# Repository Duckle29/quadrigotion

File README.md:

Quadrigotion: Multiple Motor Drivers, two connectors
============================================================

Often it is useful to have all the motor drivers needed for a machine
on a separate circuit board to be able to mount it to a heatsink or close
to the action. This is what this project is about.
The name **Quadrigotion** is a word amalgamated from 'Quadriga' (Four
horses powering a chariot) and 'Motion'.

Motivation for this project to have motor drivers easily replacable and
testable on my various 3D printers and CNC machines. Since I am also
[developing motion control software][BeagleG], I might have an unusual
high demand for this :)

The idea is to have a common connector type, described below, and various
implementations of that concept. The first implementation is using a TMC2660,
which is the 'big brother' of the more well-known TMC2100.

Other implementations are conceivable e.g. with Pololu modules, DRV8825, or
super high current and voltage drivers for heavy CNC machines.
Implementations can be super bare-bone and not use the SPI connection or
could be configured via SPI using a shift-register and digital potentiometers
if the chips can't be configured with SPI directly.
While the first Quadrigotion implementation happens to also have four motor
drivers, this could of course extend in the future.

The Connector
--------------

##TO BE EDITED TO REFLECT USE OF SMOOTHIE GADGETEER PORTS

The digital input is provided with an IDC connector with 16 pins (2x8) or
20 pins (2x10).
It features a SPI bus to send configuration data and also read motor/driver
status (the actual protocol is of implementation-dependent, but they all can
share the same hardware interface).

| Desc               | Pin | Pin | Desc
|-------------------:|:---:|:---:|:-----------------------------
|               GND  |   1 |   2 | VCC (3.3V-5V)
| All Motors ~Enable |   3 |   4 | (not connected; reserved for fault-out)
|          ~CS (SPI) |   5 |   6 | CLK (SPI)
|         MISO (SPI) |   7 |   8 | MOSI (SPI)
|            Step #1 |   9 |  10 | Dir #1
|            Step #2 |  11 |  12 | Dir #2
|            Step #3 |  13 |  14 | Dir #3
|            Step #4 |  15 |  16 | Dir #4 -------- END IDC 16 variant
|            Step #5 |  17 |  18 | Dir #5
|            Step #6 |  19 |  20 | Dir #6 -------- END IDC 20 variant

It is easy to see that extending the driver count would just require a wider
IDC connector; the serial configuration interface can deal with any
number. A 16 pin IDC connector allows for 4 steppers, the next configuration
with 20 pins would allow for six drivers.

A single Enable-pin is provided that affects all drivers. This makes it easy
to wire up that signal directly e.g. for emergency buttons.
If more individual control of each driver is needed, this can be done via
the SPI connection.

The fast signals for each stepper, step and dir, are provided in
a parallel input with two lines per stepper.

A Quadrigotion connector has a single ChipSelect signal; multiple drivers
on each implementation have to share that bus, e.g. by internally being
organized as a shift register that latches when ~CS goes high again.

One pin (pin 4) is not connected yet, but it is reserved for fault detection
output (e.g stalling, overheating or over-current).

In an upcoming project, I'll build a breakout board to work with [BeagleG].

TMC2660 Implementation
----------------------

The first implementation is based on the TMC2660, a feature-rich motor driver
that can drive up to 4A (2.8A RMS). The 40mmx125mm PCB is a four layer board
which duals as heat conductor for cooling. Multiple M2.5 mounting holes allow
to firmly mount it to a heatsink and get even pressure to individual silicone
heatsink pads.
Power is provided via a 4-pin JST VH connector (3.96mm pitch),
circuit protected with an automotive ATC Mini 297 blade fuse.

You find the gerbers in the [fab/](./fab) directory. Board is also
[shared on OshPark]. Cave: since this is the very first version, no
testing has been done yet with a physical board.

[BeagleG]: https://github.com/hzeller/beagleg
[shared on OshPark]: https://oshpark.com/shared_projects/M0SQCRdL

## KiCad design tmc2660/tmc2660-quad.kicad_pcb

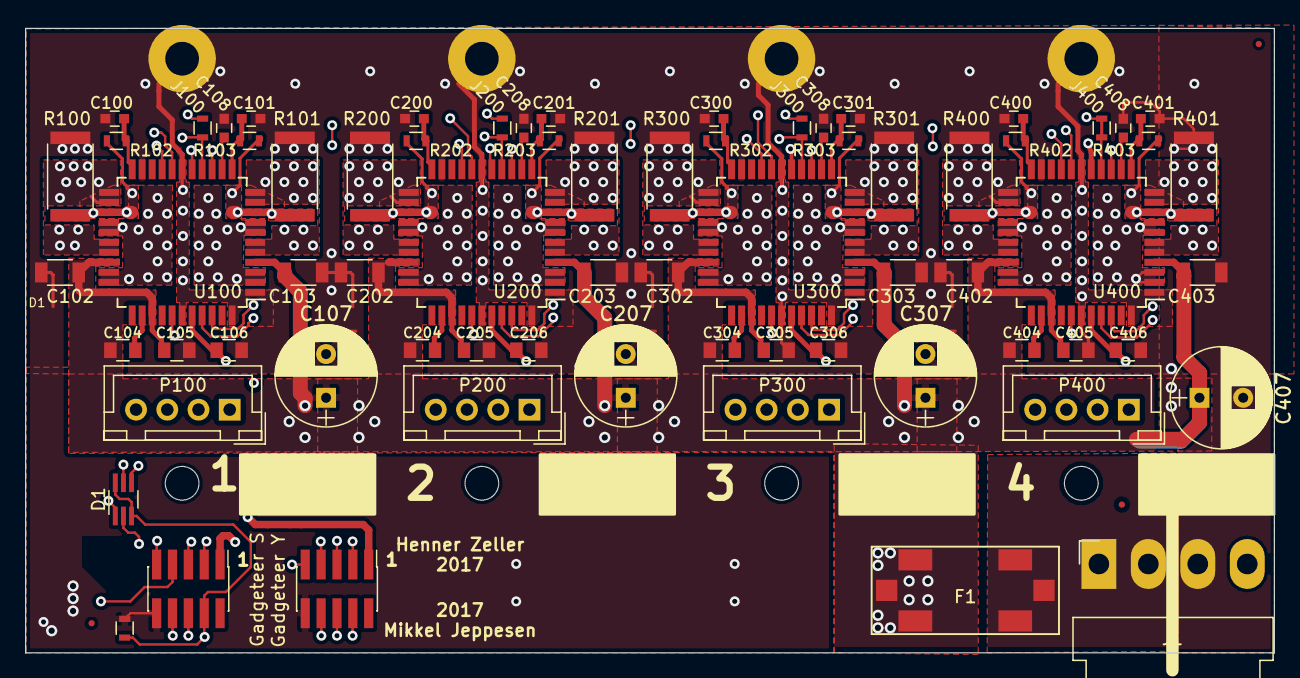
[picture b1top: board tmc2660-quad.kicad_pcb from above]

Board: 4 copper layers, 100.0 x 50.0 mm, 78 parts (0 on the bottom side), 65 nets.

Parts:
C100, C101, C200, C201, C300, C301, C400, C401: 10n; C_0603
C102, C103, C202, C203, C302, C303, C402, C403: 10u; C_1206
C104, C105, C106, C204, C205, C206, C304, C305, C306, C404, C405, C406: 100n; C_0805
C107, C207, C307, C407: 180u; CP_Radial_D8.0mm_P3.50mm
C108, C208, C308, C408: 470n; C_0603
D1: BAV70; SOT-363_SC-70-6_Handsoldering
F1: Fuse; BladeFuse-Mini_Keystone-3586
J1: Power; JST_VH_B4PS-VH_2x4x3.96mm_Horizontal
J2: Gadgeteer S; Pin_Header_Straight_2x05_Pitch1.27mm_SMD
J3: 10k; R_0603
J4: Gadgeteer Y; Pin_Header_Straight_2x05_Pitch1.27mm_SMD
J100, J200, J300, J400: 0R; R_0603
M0, M100, M200, M300: Mount; MountingHole_2.7mm_M2.5
M1, M101, M201, M301: Mount; MountingHole_2.7mm_M2.5_Pad
P100, P200, P300, P400: Motor; JST_XH_B04B-XH-A_04x2.50mm_Straight
R100, R101, R200, R201, R300, R301, R400, R401: 0.075; R_2512
R102, R103, R202, R203, R302, R303, R402, R403: 10R; R_0603
U100, U200, U300, U400: TMC2660; LQFP-44_10x10mm_Pitch0.8mm

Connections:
+3V3: C106.1, C206.1, C306.1, C406.1, J2.1, J4.1, U100.40, U200.40, U300.40, U400.40
/PowerIn: F1.2, J1.1, J1.2
/TMC2660-100/A1: P100.2, U100.2, U100.3, U100.7, U100.8
/TMC2660-100/A2: P100.1, U100.5, U100.6, U100.10, U100.11
/TMC2660-100/B1: P100.3, U100.26, U100.27, U100.31, U100.32
/TMC2660-100/B2: P100.4, U100.23, U100.24, U100.28, U100.29
/TMC2660-100/BRA: R101.1, R103.2, U100.9
/TMC2660-100/BRB: R100.1, R102.1, U100.25
/TMC2660-100/STALL: D1.2, U100.38
/TMC2660-100/VHS: C104.2, U100.35
/TMC2660-200/A1: P200.2, U200.2, U200.3, U200.7, U200.8
/TMC2660-200/A2: P200.1, U200.5, U200.6, U200.10, U200.11
/TMC2660-200/B1: P200.3, U200.26, U200.27, U200.31, U200.32
/TMC2660-200/B2: P200.4, U200.23, U200.24, U200.28, U200.29
/TMC2660-200/BRA: R201.1, R203.2, U200.9
/TMC2660-200/BRB: R200.1, R202.1, U200.25
/TMC2660-200/MISO: J100.2, U100.15, U200.14
/TMC2660-200/STALL: D1.1, U200.38
/TMC2660-200/VHS: C204.2, U200.35
/TMC2660-300/A1: P300.2, U300.2, U300.3, U300.7, U300.8
/TMC2660-300/A2: P300.1, U300.5, U300.6, U300.10, U300.11
/TMC2660-300/B1: P300.3, U300.26, U300.27, U300.31, U300.32
/TMC2660-300/B2: P300.4, U300.23, U300.24, U300.28, U300.29
/TMC2660-300/BRA: R301.1, R303.2, U300.9
/TMC2660-300/BRB: R300.1, R302.1, U300.25
/TMC2660-300/MISO: J200.2, U200.15, U300.14
/TMC2660-300/STALL: D1.4, U300.38
/TMC2660-300/VHS: C304.2, U300.35
/TMC2660-400/A1: P400.2, U400.2, U400.3, U400.7, U400.8
/TMC2660-400/A2: P400.1, U400.5, U400.6, U400.10, U400.11
/TMC2660-400/B1: P400.3, U400.26, U400.27, U400.31, U400.32
/TMC2660-400/B2: P400.4, U400.23, U400.24, U400.28, U400.29
/TMC2660-400/BRA: R401.1, R403.2, U400.9
/TMC2660-400/BRB: R400.1, R402.1, U400.25
/TMC2660-400/MISO: J300.2, U300.15, U400.14
/TMC2660-400/STALL: D1.5, U400.38
/TMC2660-400/VHS: C404.2, U400.35
CS: J2.6, U100.18, U200.18, U300.18, U400.18
DIR1: J4.6, U100.41
DIR2: J4.3, U200.41
DIR3: J4.7, U300.41
DIR4: J2.5, U400.41
GLOBAL_MISO: J2.8, U100.14
GLOBAL_MOSI: J2.7, J100.1, J200.1, J300.1, J400.1, J400.2, U400.15
GND: C100.1, C101.2, C102.2, C103.2, C105.2, C106.2, C107.2, C108.2, C200.1, C201.2, C202.2, C203.2, C205.2, C206.2, C207.2, C208.2, C300.1, C301.2, C302.2, C303.2, C305.2, C306.2, C307.2, C308.2, C400.1, C401.2, C402.2, C403.2, C405.2, C406.2, C407.2, C408.2, J1.3, J2.10, J3.2, J4.10, M1.1, M101.1, M201.1, M301.1, R100.2, R101.2, R200.2, R201.2, R300.2, R301.2, R400.2, R401.2, U100.1, U100.17, U100.21, U100.39, U100.44, U200.1, U200.17, U200.21, U200.39, U200.44, U300.1, U300.17, U300.21, U300.39, U300.44, U400.1, U400.17, U400.21, U400.39, U400.44
unnamed: C100.2, R102.2, U100.22
unnamed: C101.1, R103.1, U100.12
unnamed: C108.1, U100.13
unnamed: C200.2, R202.2, U200.22
unnamed: C201.1, R203.1, U200.12
unnamed: C208.1, U200.13
unnamed: C300.2, R302.2, U300.22
unnamed: C301.1, R303.1, U300.12
unnamed: C308.1, U300.13
unnamed: C400.2, R402.2, U400.22
unnamed: C401.1, R403.1, U400.12
unnamed: C408.1, U400.13
SCLK: J2.9, U100.16, U200.16, U300.16, U400.16
STALL: D1.3, D1.6, J2.4, J3.1
STEP1: J4.8, U100.42
STEP2: J4.4, U200.42
STEP3: J4.5, U300.42
STEP4: J4.9, U400.42
VMot: C102.1, C103.1, C104.1, C105.1, C107.1, C202.1, C203.1, C204.1, C205.1, C207.1, C302.1, C303.1, C304.1, C305.1, C307.1, C402.1, C403.1, C404.1, C405.1, C407.1, F1.1, U100.4, U100.30, U100.33, U100.36, U200.4, U200.30, U200.33, U200.36, U300.4, U300.30, U300.33, U300.36, U400.4, U400.30, U400.33, U400.36
~ENABLE: J2.3, U100.19, U200.19, U300.19, U400.19

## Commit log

2017-12-15 Started work on moving to 100x50mm design
2017-12-15 Finished squished board
2017-12-15 Fixed some mistakes pointed out
2017-12-15 Fixed break of in1 pour at R300
2017-12-15 Further fixed broken gnd pour
2017-12-27 Commiting before branching
2017-12-27 Initial commit on gadgeteer port version
2017-12-27 Added renders
2017-12-27 moved renders, added them to readme
2017-12-27 Updated readme to reflect the two conenctors used for smoothie
2018-03-04 Removed vmot-minipours, uppded BRA/BRB pours priority
